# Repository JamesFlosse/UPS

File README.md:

# vigitronic
PCB CAD Files
"# UPS" 

\\Design UPS for Raspberry//
Use for Vigibot

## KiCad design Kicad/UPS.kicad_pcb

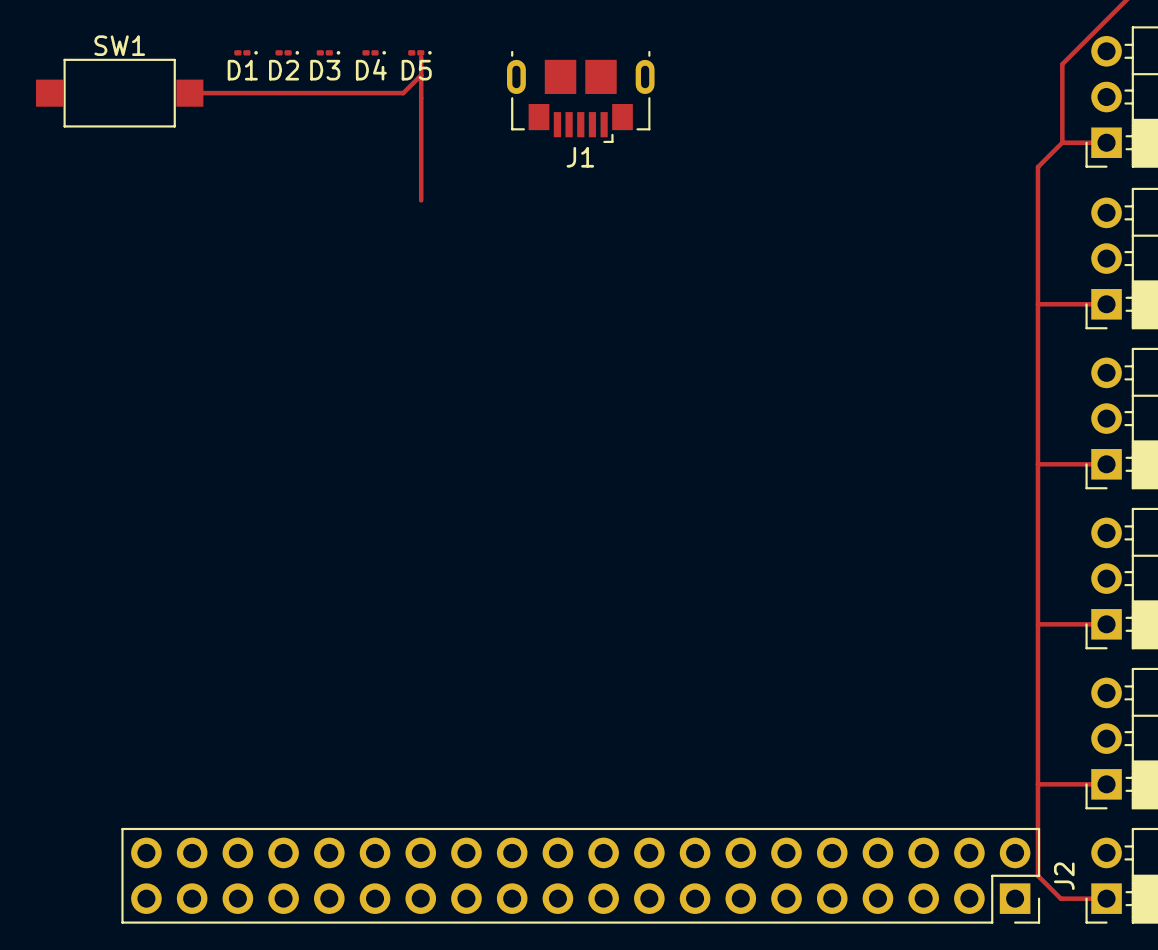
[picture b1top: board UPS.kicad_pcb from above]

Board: 2 copper layers, 14 parts (0 on the bottom side), 12 nets.

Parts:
D1, D2, D3, D4, D5: LED; LED_01005_0402Metric
J1: USB_B_Micro; USB_Micro-B_GCT_USB3076-30-A
J2: Conn_02x20_Odd_Even; PinSocket_2x20_P2.54mm_Vertical
J3: GET_UP_SERVO_RIGHT; PinSocket_1x03_P2.54mm_Horizontal
J4: Conn_01x02_Male; PinSocket_1x02_P2.54mm_Horizontal
J5, J6: Y_HEAD_PAN; PinSocket_1x03_P2.54mm_Horizontal
J7: X_CLAW; PinSocket_1x03_P2.54mm_Horizontal
J8: Y_CLAWN; PinSocket_1x03_P2.54mm_Horizontal
SW1: SW_Push; SW_SPST_CK_RS282G05A3

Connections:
+3.3V: J2.1, J2.17
+5V: J2.2, J2.4, J3.2, J4.2, J5.2, J6.2, J7.2, J8.2
GND: D5.1, J1.5, J1.6, J2.6, J2.9, J2.14, J2.20, J2.25, J2.30, J2.34, J2.39, J3.1, J4.1, J5.1, J6.1, J7.1, J8.1, SW1.2
GPIO05: J2.29, J5.3
GPIO06: J2.31, J6.3
GPIO07: J2.26, J7.3
GPIO08: J2.24, J8.3
GPIO13: J2.33, J3.3
NC: J1.2, J1.3, J1.4
unnamed: D1.1, D2.2, D3.1, D4.2
unnamed: D1.2, D2.1
unnamed: D3.2, D4.1

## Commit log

2019-08-19 Start design
2019-08-19 Add ip5306 component
2019-08-19 Add eta1096 component
2019-08-19 Placing component
2019-08-19 Connect all chipset
2019-08-19 Wiring all chip
2019-08-19 Add word
2019-08-20 Add label
2019-08-22 Add Raspberry connector with all label marked
2019-08-22 Minor change
2019-08-22 Start add footprint
2019-08-25 Add Datasheet of IP5306
2019-08-26 Minor update
2019-08-26 Add usb footprint
